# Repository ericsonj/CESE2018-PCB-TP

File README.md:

# r1.0

Primera entrega para revision.

# Progreso

## Imagen 1

## Imagen 2

# CESE2018-PCB-TP
CESE 2018 Diseño de Circuitos Impresos,

Repositorio del trabajo final del curso de Diseño de Circuitos Impresos 
de la carrera Especializacion en Sistemas embebidos. 

## Introduccion 

El siguiente proyecto busca ser un adicional al trabajo final de la carrera de especialización en sistemas embebidos
"Diseño e implementación de un sistema de comunicación VoIP usando una plataforma ARM Cortex M7**. El proyecto propone el diseño de un sheild compatible con los conectores Arduino UNO y que conecte e integra los módulos necesarios para el desarrollo del proyecto final de carrera. Estos módulos son: 

1.  AUDIO CODEC WM8731.
2.  ESP-12. 
3.  Fuente DC. 

## Objetivos

*  Diseñar un circuito impreso en Kicad que conecte los diferentes modulos de forma apropiada.

## Alcances

*  Diseño de circuito impreso.

## Posibles alcances

*  Manufactura del cicuito impreso.

## Plan de trabajo

1.  Diseño de plataforma que por medio de conectores integra en una misma placa cada modulo.
2.  Primera versión del diseño de la PCB.
3.  **Búsqueda de esquemático de modulo NODE MCU para extraer ESP-12 e integrarlo en el diseño del circuito.
4.  **Segunda versión del diseño de la PCB.
5.  **Búsqueda de esquemático de Fuente DC para integración en el circuito impreso.
6.  **Tercera versión del diseño de la PCB.
7.  **Búsqueda de esquemático de AUDIO CODEC WM8131 para integración en el circuito impreso.
8.  **Cuarta versión del diseño de la PCB.

**Posibles versiones del proyecto si alcanza el tiempo estimado. 

## Prototipo

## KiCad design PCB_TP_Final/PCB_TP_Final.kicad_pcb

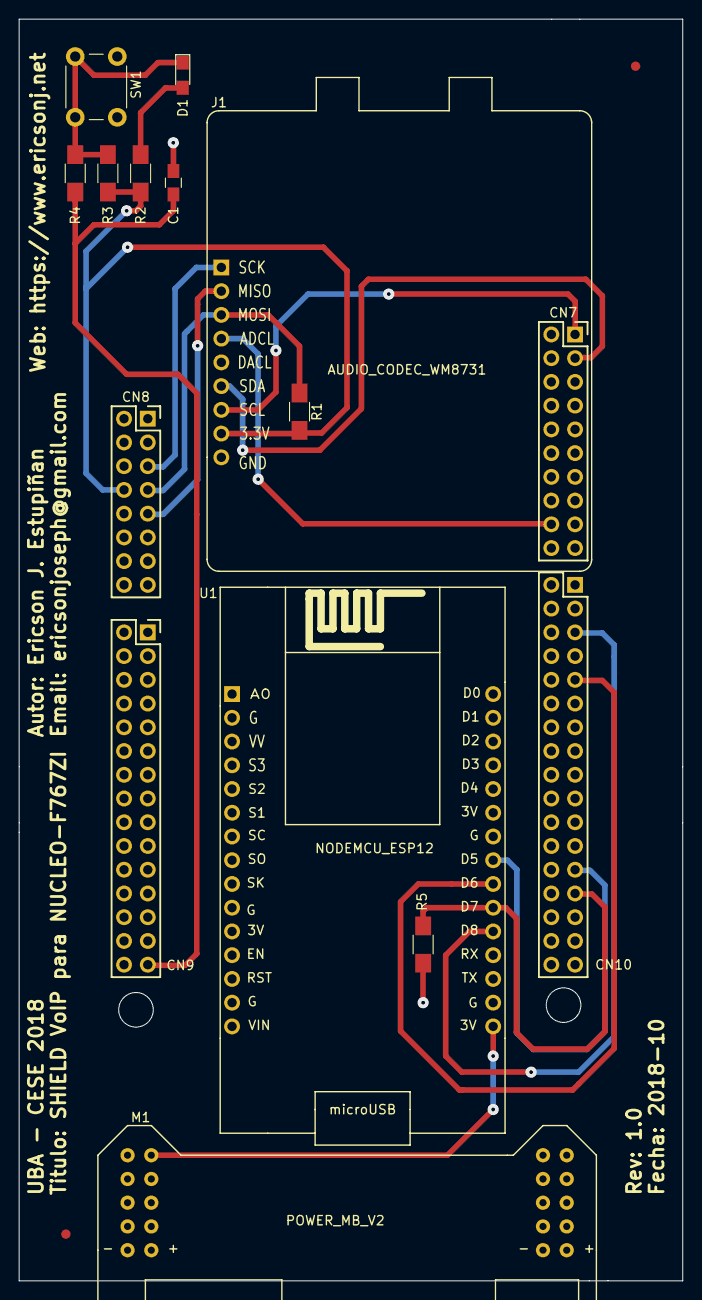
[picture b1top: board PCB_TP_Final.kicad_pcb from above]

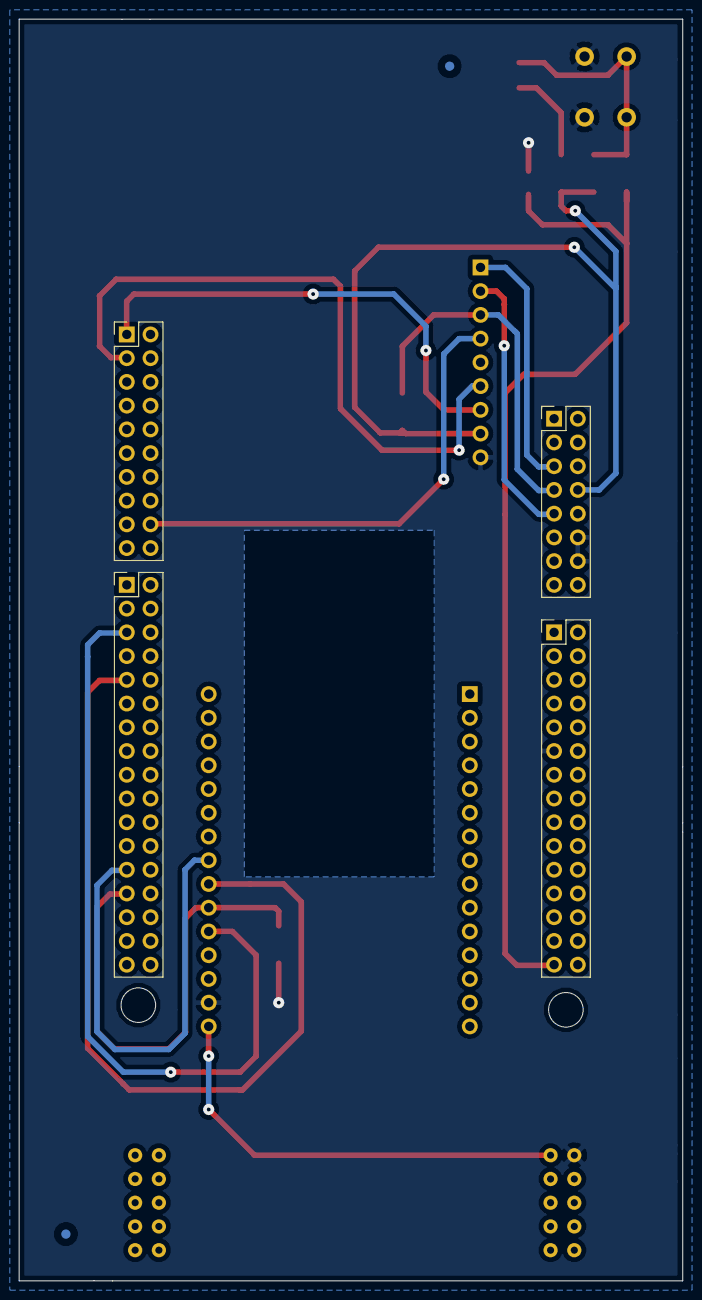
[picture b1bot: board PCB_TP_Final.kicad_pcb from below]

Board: 2 copper layers, 71.0 x 135.0 mm, 21 parts (4 on the bottom side), 16 nets.

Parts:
C1: 0.1uF; C_0805_HandSoldering
CN7: Conn_02x10_Odd_Even; Pin_Header_Straight_2x10_Pitch2.54mm
CN8: Conn_02x08_Odd_Even; Pin_Header_Straight_2x08_Pitch2.54mm
CN9: Conn_02x15_Odd_Even; Pin_Header_Straight_2x15_Pitch2.54mm
CN10: Conn_02x17_Odd_Even; Pin_Header_Straight_2x17_Pitch2.54mm
D1: LED; LED_0805_HandSoldering
F1, F2: Fiducial; Fiducial_1mm_Dia_2.54mm_Outer_CopperBottom
F3, F4: Fiducial; Fiducial_1mm_Dia_2.54mm_Outer_CopperTop
J1: Conn_01x09; Audio_Codec_WM8731
M1: POWER_MB_V2
MK1, MK2: Mounting_Hole; MountingHole_3.7mm
R1: 3.3K; R_1206_HandSoldering
R2: 330; R_1206_HandSoldering
R3: 100K; R_1206_HandSoldering
R4, R5: 10K; R_1206_HandSoldering
SW1: SW_Push; SW_PUSH_6mm_h8mm
U1: NODEMCU_ESP12

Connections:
+3.3VA: CN8.8, J1.8, R1.2, R2.2, R3.2
+3V3: M1.2, U1.16
/AUDIO_CODEC/ADCL: CN7.18, J1.4
/AUDIO_CODEC/MISO: CN8.9, J1.2
/AUDIO_CODEC/MOSI: CN8.7, J1.3, R1.1
/AUDIO_CODEC/SCK: CN8.5, J1.1
/AUDIO_CODEC/SCL: CN7.1, J1.7
/AUDIO_CODEC/SDA: CN7.3, J1.6
/NODEMCU_ESP12/HCS: CN10.5, U1.20
/NODEMCU_ESP12/HMISO: CN10.9, U1.22
/NODEMCU_ESP12/HMOSI: CN10.27, R5.1, U1.21
/NODEMCU_ESP12/HSCLK: CN10.25, U1.23
/TalkButton/talk: C1.1, CN9.29, R4.1
GND: C1.2, CN8.12, CN8.14, CN9.11, J1.9, M1.1, R5.2, SW1.2, U1.17
unnamed: D1.1, R3.1, R4.2, SW1.1
unnamed: D1.2, R2.1

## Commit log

2018-09-08 Add project info
2018-09-08 Add imagen
2018-09-08 Add show imagen proto
2018-09-08 Edit image
2018-09-08 Add working plan
2018-09-22 Init project
2018-09-22 Add footprint CODEC_AUDIO_WM8731
2018-09-22 Add 3D conections and NODEMCU ESP12
2018-09-27 Primera entrega (1.0) para revision
2018-09-27 Add image
2018-10-09 Add size modify and mounting holes
2018-10-13 Revisión 2.0 para evaluación
2018-10-21 Se agregaron correcciones sugeridas
2018-10-21 Versión lista para revisión
2018-11-13 para fabricar
2018-11-23 Add changes in via size and power track size
